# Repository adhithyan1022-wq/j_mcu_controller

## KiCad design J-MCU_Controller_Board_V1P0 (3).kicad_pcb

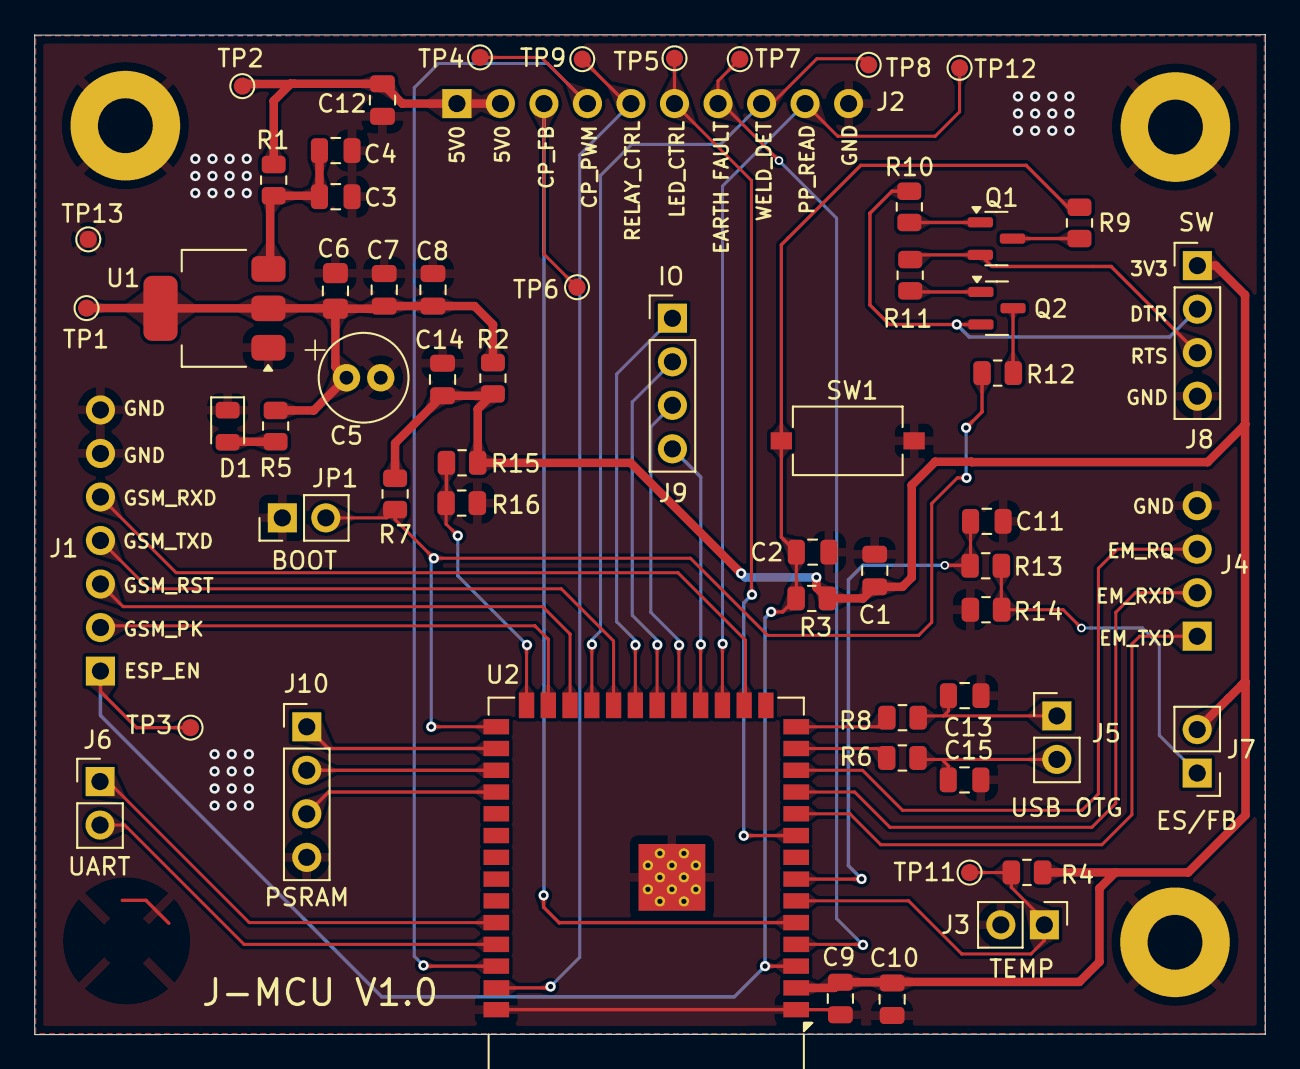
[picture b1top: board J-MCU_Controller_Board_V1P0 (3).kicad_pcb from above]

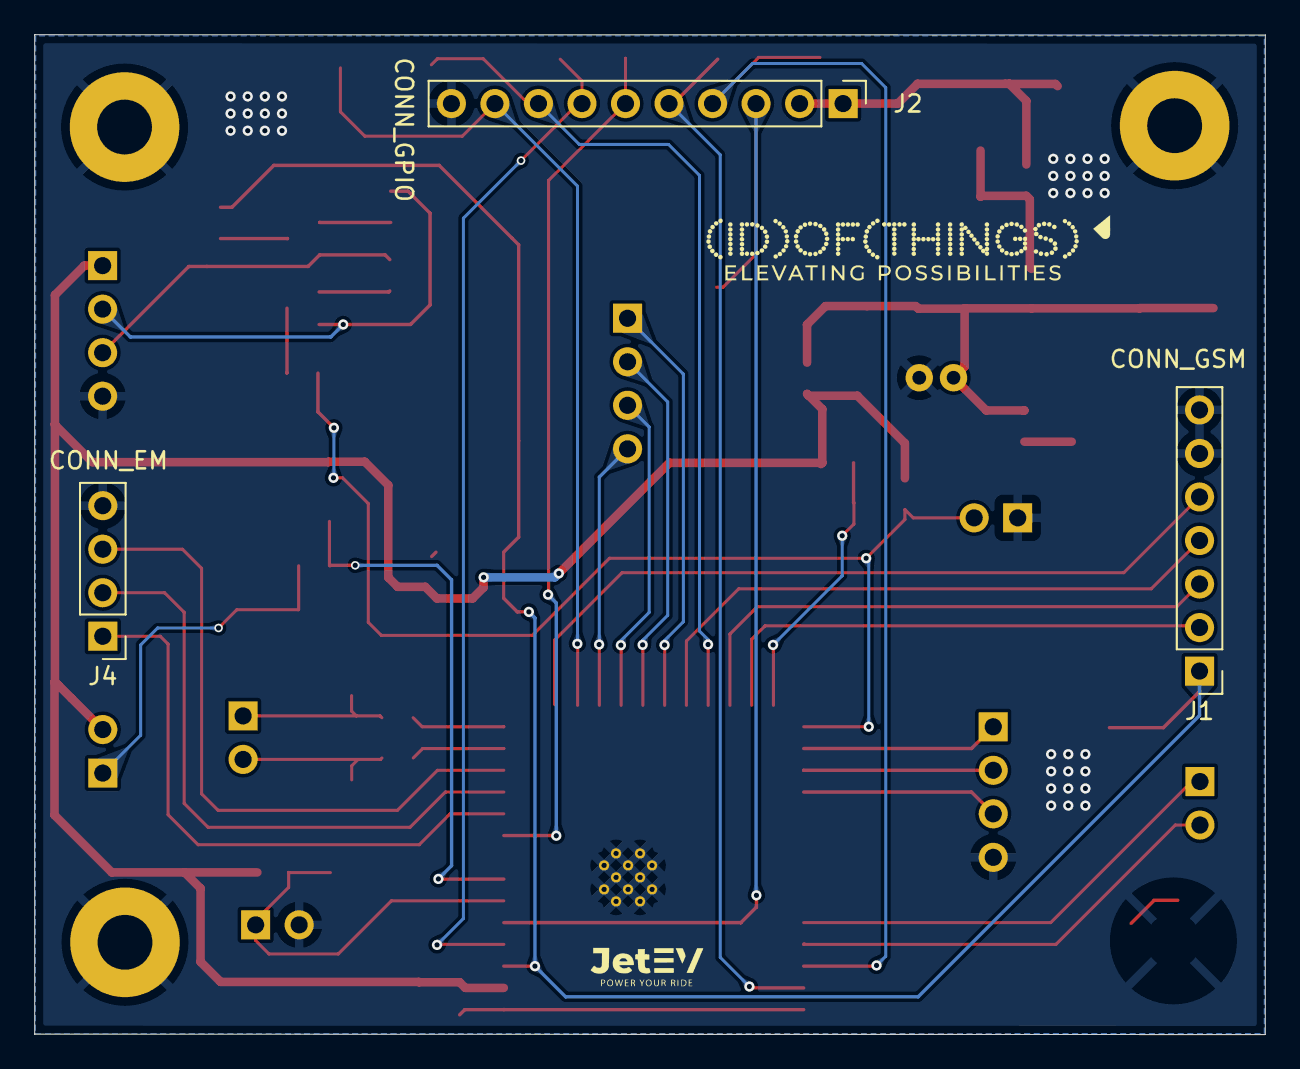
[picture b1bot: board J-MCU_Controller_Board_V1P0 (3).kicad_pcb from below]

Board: 2 copper layers, 71.8 x 58.4 mm, 63 parts (3 on the bottom side), 45 nets.

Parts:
C1, C2: 1uF; C_0805_2012Metric
C3: 10uF; C_0805_2012Metric
C4, C7, C8, C9, C11, C12, C13, C14, C15: 0.1uF; C_0805_2012Metric
C5: 100uF; C_Radial_D5.0mm_H11.0mm_P2.00mm
C6: 1uF; C_0805_2012Metric_Pad1.18x1.45mm_HandSolder
C10: 22uF; C_0805_2012Metric
D1: LED; LED_0805_2012Metric
H1, H2, H4: MountingHole_Pad; MountingHole_3.2mm_M3_Pad
J1: CONN_GSM; PinHeader_1x07_P2.54mm_Vertical
J2: CONN_GPIO; PinHeader_1x10_P2.54mm_Vertical
J3: TEMP; PinHeader_1x02_P2.54mm_Vertical
J4: CONN_EM; PinHeader_1x04_P2.54mm_Vertical
J5: USB OTG; PinHeader_1x02_P2.54mm_Vertical
J6: UART; PinHeader_1x02_P2.54mm_Vertical
J7: ES/FB; PinHeader_1x02_P2.54mm_Vertical
J8: SW; PinHeader_1x04_P2.54mm_Vertical
J9: IO; PinHeader_1x04_P2.54mm_Vertical
J10: PSRAM; PinHeader_1x04_P2.54mm_Vertical
JP1: CONN_2P; PinHeader_1x02_P2.54mm_Vertical
Q1, Q2: S8050W; SOT-23
R1, R2, R6, R8, R9, R12, R13: 0R; R_0805_2012Metric
R3, R4, R7, R10, R11, R14, R15, R16: 10K; R_0805_2012Metric
R5: 2.2K; R_0805_2012Metric
SW1: SW_SPST; SW_Tactile_SPST_NO_Straight_CK_PTS636Sx25SMTRLFS
TP1, TP2, TP3, TP4, TP5, TP6, TP7, TP8, TP9, TP11, TP12, TP13: TestPoint; TestPoint_Pad_D1.0mm
U1: AMS1117-3.3; SOT-223-3_TabPin2
U2: ESP32-S3-WROOM-1

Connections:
/Controller/BOOTMODE: JP1.2 (B), R7.1, R12.1, U2.27 (IO0)
/Controller/CONN_D+: C13.2, J5.1, R8.2
/Controller/CONN_D-: C15.2, J5.2, R6.2
/Controller/CP_FB: J2.3, TP6.1, U2.5 (IO5)
/Controller/CP_PWM: J2.4, TP4.1, U2.38 (IO2)
/Controller/DTR: J8.2, Q2.2 (E), R10.1
/Controller/EARTH_FAULT_INPUT: J2.7, TP7.1, U2.4 (IO4)
/Controller/ESP_EN: C2.2, J1.1, R3.1, R9.1, SW1.1 (A), TP3.1, U2.3 (EN)
/Controller/ESP_UART0_RX: J6.1, U2.36 (RXD0)
/Controller/ESP_UART0_TX: J6.2, U2.37 (TXD0)
/Controller/ES/FB: C11.2, R13.1, U2.7 (IO7)
/Controller/GPIO10: J9.4, U2.18 (IO10)
/Controller/GPIO11: J9.3, U2.19 (IO11)
/Controller/GPIO12: J9.2, U2.20 (IO12)
/Controller/GPIO13: J9.1, U2.21 (IO13)
/Controller/GPIO35: J10.1, U2.28 (IO35)
/Controller/GPIO36: J10.2, U2.29 (IO36)
/Controller/GPIO37: J10.3, U2.30 (IO37)
/Controller/GSM_P_K: J1.2, U2.25 (IO48)
/Controller/GSM_RST: J1.3, U2.24 (IO47)
/Controller/GSM_RXD: J1.5, U2.16 (IO46)
/Controller/GSM_TXD: J1.4, U2.22 (IO14)
/Controller/IO45: R15.2, R16.1, U2.26 (IO45)
/Controller/LED_CTRL: J2.6, TP5.1, U2.9 (IO16)
/Controller/MCU_EM_IRQ: J4.3, U2.12 (IO8)
/Controller/MCU_EM_RXD: J4.2, U2.11 (IO18)
/Controller/MCU_EM_TXD: J4.1, U2.10 (IO17)
/Controller/PP_READ: J2.9, TP12.1, U2.17 (IO9)
/Controller/RELAY_CTRL: J2.5, TP9.1, U2.39 (IO1)
/Controller/RTS: J8.3, Q1.2 (E), R11.1
/Controller/TEMP_PROBE: J3.1, R4.1, TP11.1, U2.6 (IO6)
/Controller/USB_D+: R8.1, U2.14 (IO20)
/Controller/USB_D-: R6.1, U2.13 (IO19)
/Controller/WELD_DET: J2.8, TP8.1, U2.23 (IO21)
GND: C1.1, C2.1, C3.1, C4.1, C5.2, C6.1, C7.1, C8.1, C9.2, C10.2, C11.1, C12.2, C13.1, C14.1, C15.1, D1.1 (K), H1.1, H2.1, H4.1, J1.6, J1.7, J2.10, J3.2, J4.4, J8.4, J10.4, JP1.1 (A), R14.2, R16.2, SW1.2 (B), TP13.1, U1.1 (GND), U2.1 (GND), U2.40 (GND), U2.41 (GND)
unnamed: D1.2 (A), R5.2
unnamed: J7.1, R13.2, R14.1
unnamed: Q1.1 (B), R10.2
unnamed: Q1.3 (C), R9.2
unnamed: Q2.1 (B), R11.2
unnamed: Q2.3 (C), R12.2
unnamed: C3.2, C4.2, R1.2, U1.3 (VI)
unnamed: C5.1, C6.2, C7.2, C8.2, R2.2, R5.1, TP1.1, U1.2 (VO)
VCC_5V0: C12.1, J2.1, J2.2, R1.1, TP2.1
VDD_MCU_3V3: C1.2, C9.1, C10.1, C14.2, J7.2, J8.1, R2.1, R3.2, R4.2, R7.2, R15.1, U2.2 (3V3)

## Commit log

2025-09-08 add new features
2025-09-08 Add files via upload
    fdhgskjh
2025-09-08 Add files via upload
    the wae
